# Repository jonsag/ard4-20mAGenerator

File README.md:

# ard4-20mAGenerator

Generate and measure 4-20mA signals

## Links

[4-20ma Generator/Tester Using Arduino by PieterB14 @ Instructables](https://www.instructables.com/4-20ma-GeneratorTester-Using-Arduino/)  

[Handheld Voltage and Current Source 4-20mA by lawsonkeith @ Instructables](https://www.instructables.com/Handheld-Current-and-Voltage-Source/)  

[SIMULANT - Remotely Controlled Multi Purpose Simulator 4-20mA, PT100, Pulse Generator and Counter by bcsedlon @ Instructables](https://www.instructables.com/SIMULANT-Remotely-Controlled-Multi-Purpose-Simulat/)

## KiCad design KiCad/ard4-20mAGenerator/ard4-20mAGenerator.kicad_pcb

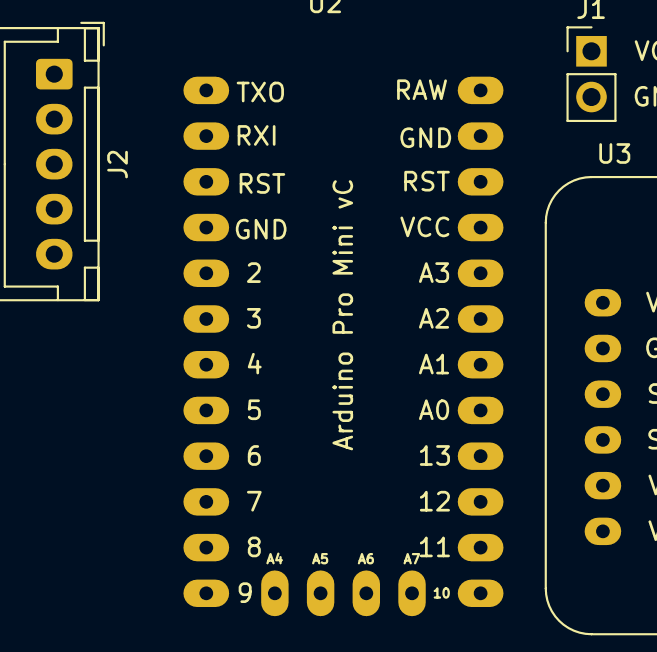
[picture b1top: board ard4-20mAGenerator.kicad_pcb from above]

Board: 2 copper layers, 4 parts (0 on the bottom side), 8 nets, no tracks yet.

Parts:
J1: 2-pin_power_input_header
J2: 5-pin_LCD; 5-pin JST LCD
U2: Arduino_Mini_Pro; Arduino_Pro_Mini_vC_no-progr-large
U3: module_ina219

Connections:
+5V: J2.4 (+5V), U2.16 (VCC), U3.1 (VCC)
GND: J1.2 (GND), J2.5 (GND), U2.4 (GND), U2.14 (GND), U3.2 (GND)
unnamed: J2.1 (Data), U2.5 (2)
unnamed: J2.2 (Latch), U2.6 (3)
unnamed: J2.3 (Clock), U2.7 (4)
unnamed: U2.25 (A4), U3.4 (SDA)
unnamed: U2.26 (A5), U3.3 (SCL)
VCC: J1.1 (VCC), U2.13 (RAW)

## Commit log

2023-02-21 kicad 7
